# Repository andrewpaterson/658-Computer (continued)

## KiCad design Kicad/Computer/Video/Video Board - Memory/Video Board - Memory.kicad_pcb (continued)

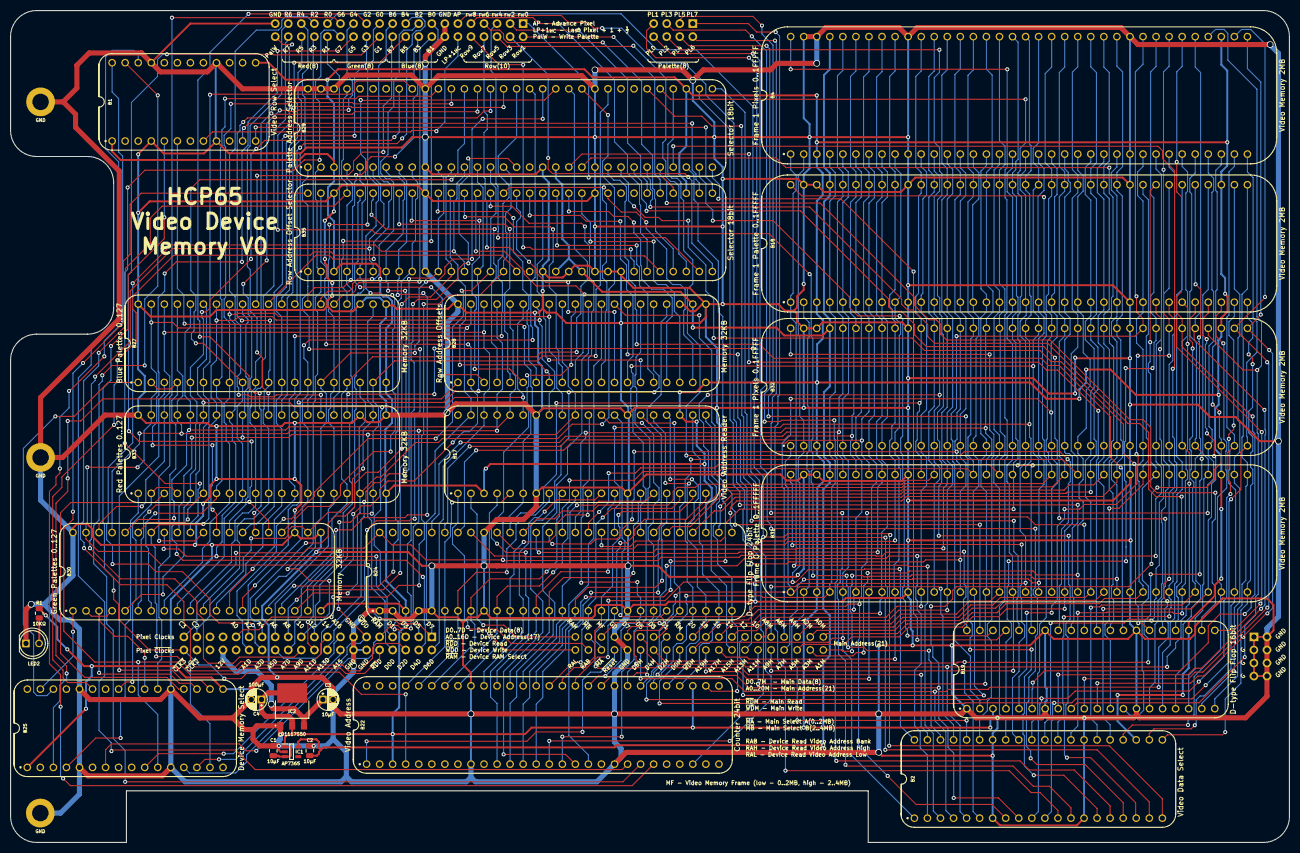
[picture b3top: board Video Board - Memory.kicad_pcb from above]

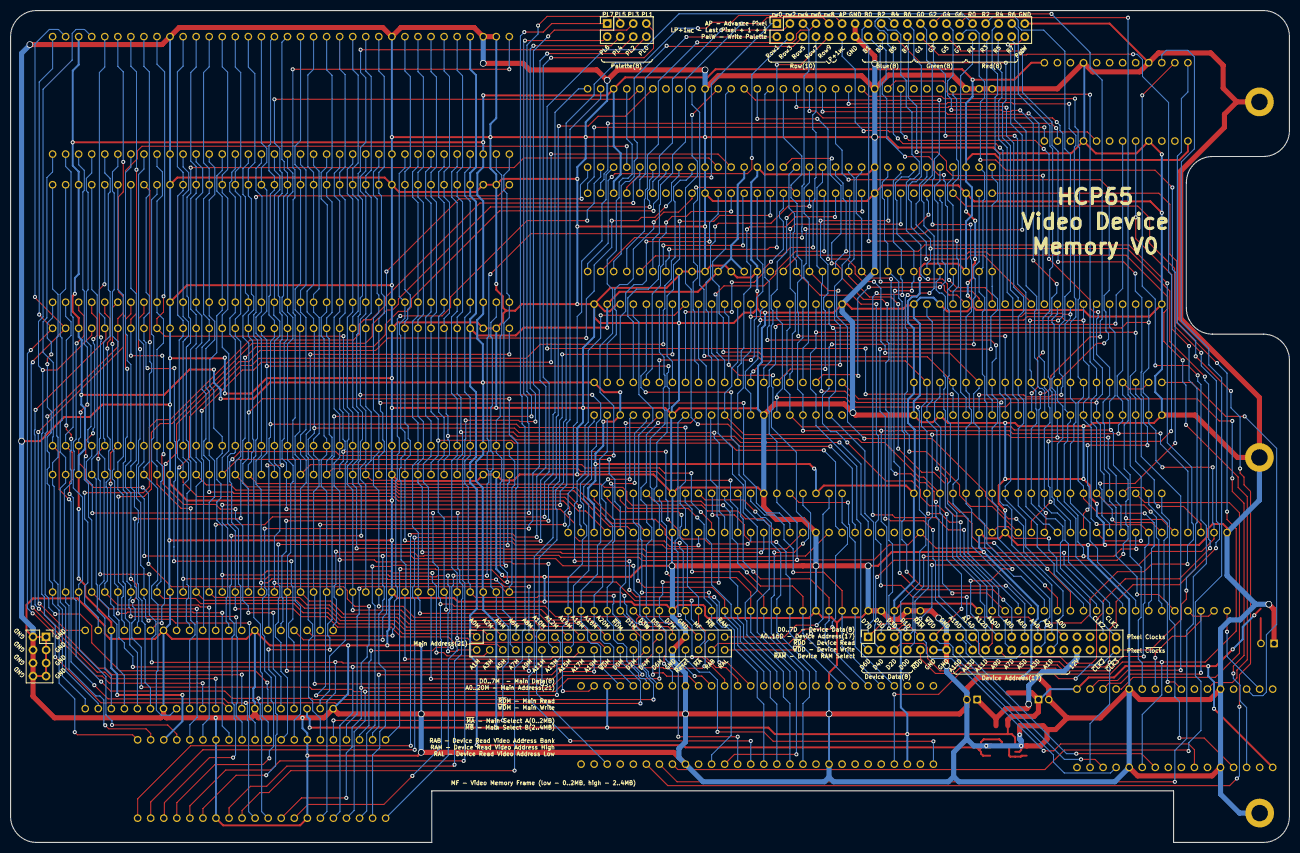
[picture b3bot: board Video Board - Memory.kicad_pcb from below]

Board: 2 copper layers, 248.9 x 161.9 mm, 33 parts (5 on the bottom side), 263 nets.

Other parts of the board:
J5: Conn_01x08_Pin; PinSocket_2x04_P2.54mm_Vertical

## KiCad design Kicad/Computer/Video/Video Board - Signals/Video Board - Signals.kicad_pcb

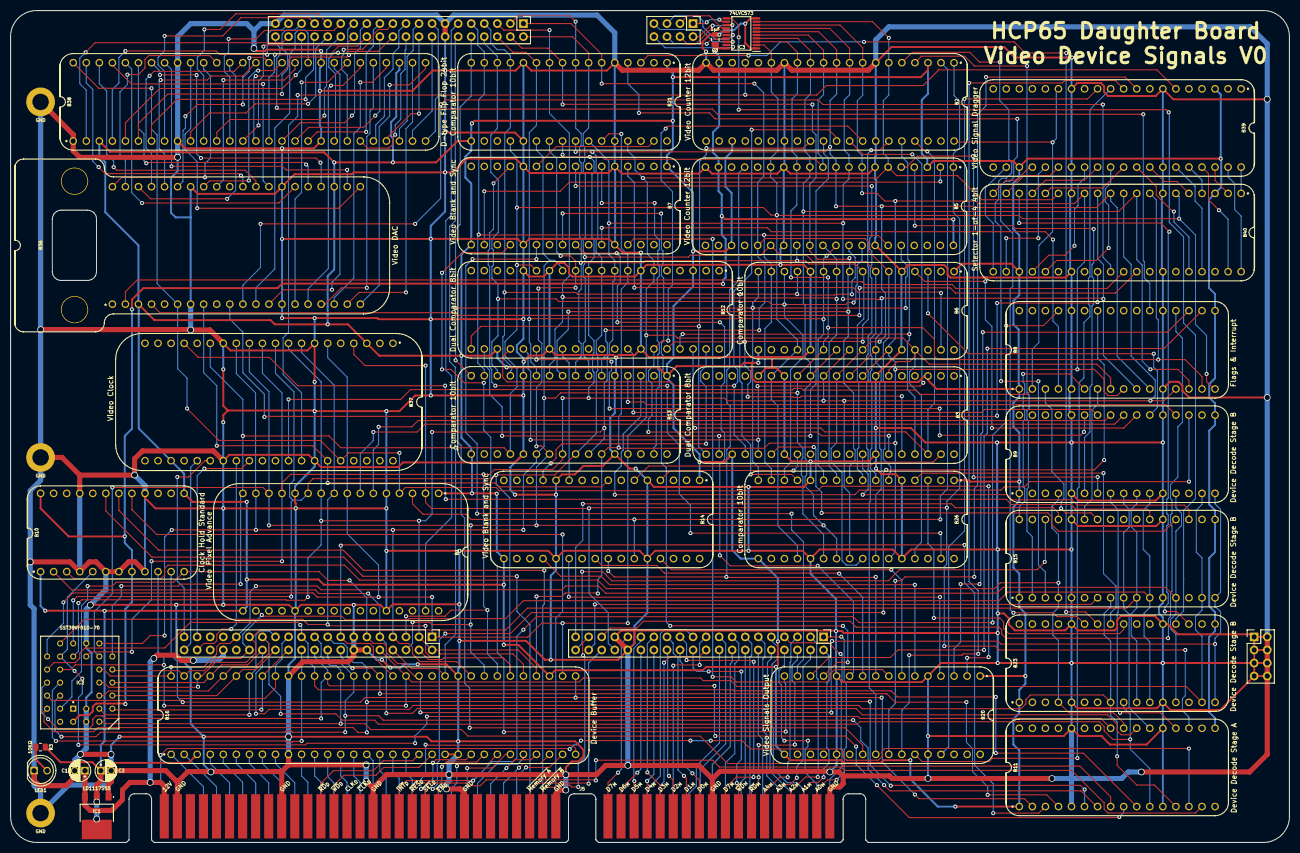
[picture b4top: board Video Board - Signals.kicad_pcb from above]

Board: 2 copper layers, 248.9 x 161.9 mm, 41 parts (0 on the bottom side), 268 nets.

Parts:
B1: Video Pixel Advance; HCP65_Video_Pixel_Advance
B2, B5: Video Counter 12bit; HCP65_Video_Counter_12bit
B3, B12: Dual Comparator 8bit; HCP65_Dual_Comparator_8bit
B6, B13, B21, B26: Comparator 10bit; HCP65_Comparator_10bit
B7, B14: Video Blank and Sync; HCP65_Video_Blank_and_Sync
B8: Flags & Interrupt; HCP65_Flags_Interrupt
B9, B15, B23: Device Decode Stage B; HCP65_Device_Decode_Stage_B
B10: Clock Hold Standard; HCP65_Clock_Hold_Standard
B11: Device Decode Stage A; HCP65_Device_Decode_Stage_A
B16: Device Buffer; HCP65_Device_Buffer
B20: Video Signals Output; HCP65_Video_Output_Signals
B36: Video DAC; HCP65_Video_DAC
B37: Video Clock; HCP65_Video_Clock
B38: D-type Flip Flop 24bit; HCP65_D_Flip_Flop_24bit
B39: Video Signal Dragger; HCP65_Video_Signal_Dragger
B40: Selector 1-of-4 4bit with Input; HCP65_Selector_1_of_4_4bit_with_Input
C1: 10μF; CP_Radial_D4.0mm_P2.00mm
C2: 100μF; CP_Radial_D4.0mm_P2.00mm
C3: 1μF; C_0805
H1, H9, H19: MountingHole_Pad; HCP65_MountingHole_M3_
IC1: LD1117S50C; LD1117S33C
IC2: SST39VF010-70-4I-NHE; 5408803224008
IC3: 74LVC573APW,118; SOP65P640X110-20N
J1, J6: Conn_01x08_Pin; PinHeader_2x04_P2.54mm_Vertical
J2, J3, J4: Conn_01x40_Pin; PinHeader_2x20_P2.54mm_Vertical
J5: 395-098-520-350; 98pin Edge Connector
LED1: LED; LED_D5.0mm
R3: 10KΩ; R_0805

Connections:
12V: C1.1, IC1.3 (15VIn), J4.34, J5.B1
/3.3V: B2.19 (IR0), B5.19 (IR0), B5.40 (~CLK), B10.8 (H0_{REG}), B10.24 (3.3V), C3.2, IC2.32 (3V), IC3.20 (3V)
/5V: B1.1 (5V), B1.17 (5V), B2.3 (5V), B2.23 (5V), B3.3 (5V), B3.23 (5V), B5.3 (5V), B5.23 (5V), B6.1 (5V), B6.17 (5V), B7.1 (5V), B7.17 (5V), B8.1 (5V), B8.17 (5V), B9.1 (5V), B9.17 (5V), B10.1 (5V), B10.13 (5V), B11.1 (5V), B11.17 (5V), B12.3 (5V), B12.23 (5V), B13.1 (5V), B13.17 (5V), B14.1 (5V), B14.17 (5V), B15.1 (5V), B15.17 (5V), B16.3 (5V), B16.35 (5V), B20.1 (5V), B20.17 (5V), B21.1 (5V), B21.17 (5V), B23.1 (5V), B23.17 (5V), B26.1 (5V), B26.17 (5V), B36.3 (5V), B36.23 (5V), B37.3 (5V), B37.23 (5V), B38.3 (5V), B38.31 (5V), B39.3 (5V), B39.23 (5V), B40.3 (5V), B40.23 (5V), C2.1, IC1.2 (5.0VOut), IC1.4 (5.0VOut), R3.2
/A0: B9.13 (A0), B15.13 (A0), B16.64 (A0), B23.13 (A0), IC2.12 (A0), J4.31
/A1: B9.11 (A1), B15.11 (A1), B16.63 (A1), B23.11 (A1), IC2.11 (A1), J4.30
/A2: B9.10 (A2), B15.10 (A2), B16.62 (A2), B23.10 (A2), IC2.10 (A2), J4.29
/A3: B11.13 (A3), B15.8 (~E2), B16.61 (A3), B23.8 (~E2), IC2.9 (A3), J4.28
/A4: B11.11 (A4), B16.60 (A4), B23.9 (E3), IC2.8 (A4), J4.27
/A5: B16.59 (A5), IC2.7 (A5), J4.26
/A6: B16.58 (A6), IC2.6 (A6), J4.25
/A7: B16.57 (A7), IC2.5 (A7), J4.24
/A8: B16.56 (A8), IC2.27 (A8), J4.23
/A9: B16.54 (A9), IC2.26 (A9), J4.22
/A10: B11.10 (A10), B16.53 (A10), IC2.23 (A10), J4.21
/A11: B11.9 (A11), B16.52 (A11), IC2.25 (A11), J4.20
/A12: B11.8 (A12), B16.51 (A12), IC2.4 (A12), J4.19
/A13: B11.7 (A13), B16.50 (A13), IC2.28 (A13), J4.18
/A14: B11.6 (A14), B16.49 (A14), IC2.29 (A14), J4.17
/A15: B11.4 (A15), B16.48 (A15), J4.16
/A16: B11.3 (A16), B16.47 (A16), J4.15
/Advance Pixel: B1.31 (Selected_Pattern), J3.11
/Blue0: B38.28 (IN0), J3.15
/Blue1: B38.27 (IN1), J3.16
/Blue2: B38.26 (IN2), J3.17
/Blue3: B38.25 (IN3), J3.18
/Blue4: B38.24 (IN4), J3.19
/Blue5: B38.23 (IN5), J3.20
/Blue6: B38.22 (IN6), J3.21
/Blue7: B38.21 (IN7), J3.22
/D0: B1.16 (D0), B2.15 (D0), B3.15 (D0), B5.15 (D0), B6.20 (D0), B8.16 (D0), B12.15 (D0), B13.20 (D0), B16.43 (D7), B21.20 (D0), B26.20 (D0), B37.15 (D0), B40.6 (D0), IC2.13 (DQ0), IC3.2 (D0), J4.8
/D1: B1.15 (D1), B2.13 (D1), B3.13 (D1), B5.13 (D1), B6.22 (D1), B8.15 (D1), B12.13 (D1), B13.22 (D1), B16.41 (D6), B21.22 (D1), B26.22 (D1), B37.13 (D1), B40.8 (D1), IC2.14 (DQ1), IC3.3 (D1), J4.7
/D2: B1.14 (D2), B2.12 (D2), B3.12 (D2), B5.12 (D2), B6.23 (D2), B8.14 (D2), B12.12 (D2), B13.23 (D2), B16.40 (D5), B21.23 (D2), B26.23 (D2), B37.12 (D2), B40.9 (D2), IC2.15 (DQ2), IC3.4 (D2), J4.6
/D3: B1.13 (D3), B2.11 (D3), B3.11 (D3), B5.11 (D3), B6.24 (D3), B8.13 (D3), B12.11 (D3), B13.24 (D3), B16.39 (D4), B21.24 (D3), B26.24 (D3), B37.11 (D3), B40.10 (D3), IC2.17 (DQ3), IC3.5 (D3), J4.5
/D4: B1.11 (D4), B2.10 (D4), B3.10 (D4), B5.10 (D4), B6.25 (D4), B8.11 (D4), B12.10 (D4), B13.25 (D4), B16.38 (D3), B21.25 (D4), B26.25 (D4), B37.10 (D4), B40.11 (D4), IC2.18 (DQ4), IC3.6 (D4), J4.4
/D5: B1.10 (D5), B2.9 (D5), B3.9 (D5), B5.9 (D5), B6.26 (D5), B8.10 (D5), B12.9 (D5), B13.26 (D5), B16.37 (D2), B21.26 (D5), B26.26 (D5), B37.9 (D5), B40.12 (D5), IC2.19 (DQ5), IC3.7 (D5), J4.3
/D6: B1.9 (D6), B2.8 (D6), B3.8 (D6), B5.8 (D6), B6.27 (D6), B8.9 (D6), B12.8 (D6), B13.27 (D6), B16.36 (D1), B21.27 (D6), B26.27 (D6), B37.8 (D6), B40.13 (D6), IC2.20 (DQ6), IC3.8 (D6), J4.2
/D7: B1.8 (D7), B2.6 (D7), B3.6 (D7), B5.6 (D7), B6.29 (D7), B8.8 (D7), B12.6 (D7), B13.29 (D7), B16.34 (D0), B21.29 (D7), B26.29 (D7), B37.6 (D7), B40.15 (D7), IC2.21 (DQ7), IC3.9 (D7), J4.1
/First Pixel: B5.17 (CLK), B14.25 (First), B20.9 (First_Pixel)
/First Pixel HC: B7.8 (~CLK), B20.24 (First_Pixel_{OUT})
/First Row: B7.25 (First), B20.11 (First_Row)
/Green0: B38.19 (IN8), J3.23
/Green1: B38.18 (IN9), J3.24
/Green2: B38.17 (IN10), J3.25
/Green3: B38.16 (IN11), J3.26
/Green4: B38.15 (IN12), J3.27
/Green5: B38.14 (IN13), J3.28
/Green6: B38.13 (IN14), J3.29
/Green7: B38.12 (IN15), J3.30
/H3: B2.29 (R3), B3.21 (C0), B12.21 (C0)
/H4: B2.30 (R4), B3.22 (C1), B12.22 (C1)
/H5: B2.31 (R5), B3.24 (C2), B12.24 (C2)
/H6: B2.32 (R6), B3.25 (C3), B12.25 (C3)
/H7: B2.33 (R7), B3.35 (C4), B12.35 (C4)
/H8: B2.35 (R8), B3.36 (C5), B12.36 (C5)
/H9: B2.36 (R9), B3.37 (C6), B12.37 (C6)
/H10: B2.37 (R10), B3.38 (C7), B12.38 (C7)
/HCBlue0: B36.20 (Blue0), B38.29 (OUT0)
/HCBlue1: B36.19 (Blue1), B38.30 (OUT1)
/HCBlue2: B36.18 (Blue2), B38.32 (OUT2)
/HCBlue3: B36.17 (Blue3), B38.33 (OUT3)
/HCBlue4: B36.16 (Blue4), B38.34 (OUT4)
/HCBlue5: B36.15 (Blue5), B38.35 (OUT5)
/HCBlue6: B36.13 (Blue6), B38.36 (OUT6)
/HCBlue7: B36.12 (Blue7), B38.38 (OUT7)
/HCGreen0: B36.32 (Green0), B38.39 (OUT8)
/HCGreen1: B36.33 (Green1), B38.40 (OUT9)
/HCGreen2: B36.35 (Green2), B38.41 (OUT10)
/HCGreen3: B36.36 (Green3), B38.42 (OUT11)
/HCGreen4: B36.37 (Green4), B38.43 (OUT12)
/HCGreen5: B36.38 (Green5), B38.44 (OUT13)
/HCGreen6: B36.39 (Green6), B38.45 (OUT14)
/HCGreen7: B36.40 (Green7), B38.46 (OUT15)
/HCRed0: B36.21 (Red0), B38.47 (OUT16)
/HCRed1: B36.22 (Red1), B38.49 (OUT17)
/HCRed2: B36.24 (Red2), B38.50 (OUT18)
/HCRed3: B36.25 (Red3), B38.51 (OUT19)
/HCRed4: B36.26 (Red4), B38.52 (OUT20)
/HCRed5: B36.28 (Red5), B38.53 (OUT21)
/HCRed6: B36.29 (Red6), B38.54 (OUT22)
/HCRed7: B36.30 (Red7), B38.55 (OUT23)
/Horizontal Blank: B14.29 (Blank), B20.7 (Horizontal_Blank)
/Horizontal Blank C3: B39.33 (Horizontal_Blank__{CYCLE_3}), B40.5 (B2)
/Horizontal Blank C4: B39.24 (Horizontal_Blank__{CYCLE_4}), B40.20 (E2)
/Horizontal Blank HC: B20.27 (Horizontal_Blank_{OUT}), B39.11 (Horizontal_Blank__{HALF_CYCLE})
/Horizontal Blank HC3: B39.38 (Horizontal_Blank__{CYCLE_3H}), B40.2 (A2)
/Horizontal Blank HC4: B39.29 (Horizontal_Blank__{CYCLE_4H}), B40.17 (C2)
/Horizontal Blank _{FINAL}: B36.2 (Horizontal_Blank), B40.31 (Y1)
/Horizontal Sync: B14.22 (Sync), B20.4 (Horizontal_Sync)
/Horizontal Sync C3: B39.32 (Horizontal_Sync__{CYCLE_3}), B40.36 (B3)
/Horizontal Sync C4: B39.22 (Horizontal_Sync__{CYCLE_4}), B40.21 (E3)
/Horizontal Sync HC: B20.29 (Horizontal_Sync_{OUT}), B39.12 (Horizontal_Sync__{HALF_CYCLE})
/Horizontal Sync HC3: B39.37 (Horizontal_Sync__{CYCLE_3H}), B40.39 (A3)
/Horizontal Sync HC4: B39.28 (Horizontal_Sync__{CYCLE_4H}), B40.24 (C3)
/Horizontal Sync Polarity: B8.19 (F1), B20.3 (Horizontal_Sync_Polarity)
/Horizontal Sync _{FINAL}: B36.4 (Horizontal_Sync), B40.32 (Y0)
/Last Pixel+1: B14.24 (Last+1), B20.10 (Last_Pixel+1)
/Last Pixel+1 HC: B20.23 (Last_Pixel+1_{OUT}), J3.12
/Last Row+1: B7.24 (Last+1), B20.13 (Last_Row+1)
/Memory Frame: B8.20 (F2), J2.35
/PL0: IC3.19 (Q0), J1.8
/PL1: IC3.18 (Q1), J1.7
/PL2: IC3.17 (Q2), J1.6
/PL3: IC3.16 (Q3), J1.5
/PL4: IC3.15 (Q4), J1.4
/PL5: IC3.14 (Q5), J1.3
/PL6: IC3.13 (Q6), J1.2
/PL7: IC3.12 (Q7), J1.1
/Palette Write: B8.22 (F3), J3.40
/Pixel CLK_{0}: B1.4 (CLK), B20.2 (~Pixel_CLK), B36.6 (~CLK), B37.36 (Pixel_CLK_{0}), B38.56 (CLK)
/Pixel CLK_{1}: B2.17 (CLK), B37.33 (Pixel_CLK_{1}), B39.6 (Pixel_CLK)
/Pixel CLK_{2}: B37.29 (Pixel_CLK_{2}), J4.37
/Pixel CLK_{3}: B37.26 (Pixel_CLK_{3}), J4.39
/Read Address Bank: B15.7 (Y4_{R}), J2.38
/Read Address High: B15.29 (Y3_{R}), J2.39
/Read Address Low: B15.30 (Y2_{R}), J2.40
/Read Flags: B8.6 (Read_Flags), B15.32 (Y0_{R})
/Read Horizontal High: B2.4 (Read_Count_High), B15.2 (Y7_{R})
/Read Horizontal Low: B2.5 (Read_Count_Low), B15.3 (Y6_{R})
/Read Vertical High: B5.4 (Read_Count_High), B9.6 (Y5_{R})
/Read Vertical Low: B5.5 (Read_Count_Low), B9.7 (Y4_{R})
/Red0: B38.11 (IN16), J3.31
/Red1: B38.10 (IN17), J3.32
/Red2: B38.8 (IN18), J3.33
/Red3: B38.7 (IN19), J3.34
/Red4: B38.6 (IN20), J3.35
/Red5: B38.5 (IN21), J3.36
/Red6: B38.4 (IN22), J3.37
/Red7: B38.2 (IN23), J3.38
/Row0: B5.25 (R0), B6.6 (C0), B13.6 (C0), B21.6 (C0), B26.6 (C0), J3.1
/Row1: B5.26 (R1), B6.7 (C1), B13.7 (C1), B21.7 (C1), B26.7 (C1), J3.2
/Row2: B5.28 (R2), B6.8 (C2), B13.8 (C2), B21.8 (C2), B26.8 (C2), J3.3
/Row3: B5.29 (R3), B6.9 (C3), B13.9 (C3), B21.9 (C3), B26.9 (C3), J3.4
/Row4: B5.30 (R4), B6.10 (C4), B13.10 (C4), B21.10 (C4), B26.10 (C4), J3.5
/Row5: B5.31 (R5), B6.11 (C5), B13.11 (C5), B21.11 (C5), B26.11 (C5), J3.6
/Row6: B5.32 (R6), B6.13 (C6), B13.13 (C6), B21.13 (C6), B26.13 (C6), J3.7
/Row7: B5.33 (R7), B6.14 (C7), B13.14 (C7), B21.14 (C7), B26.14 (C7), J3.8
/Row8: B5.35 (R8), B6.15 (C8), B13.15 (C8), B21.15 (C8), B26.15 (C8), J3.9
/Row9: B5.36 (R9), B6.16 (C9), B13.16 (C9), B21.16 (C9), B26.16 (C9), J3.10
/Vertical Blank: B7.29 (Blank), B20.8 (Vertical_Blank)
/Vertical Blank C3: B39.36 (Vertical_Blank__{CYCLE_3}), B40.4 (B0)
/Vertical Blank C4: B39.26 (Vertical_Blank__{CYCLE_4}), B40.19 (E0)
/Vertical Blank HC: B20.25 (Vertical_Blank_{OUT}), B39.9 (Vertical_Blank__{HALF_CYCLE})
/Vertical Blank HC3: B39.40 (Vertical_Blank__{CYCLE_3H}), B40.1 (A0)
/Vertical Blank HC4: B39.31 (Vertical_Blank__{CYCLE_4H}), B40.16 (C0)
/Vertical Blank _{FINAL}: B36.10 (Vertical_Blank), B40.29 (Y3)
/Vertical Sync: B7.22 (Sync), B20.15 (Vertical_Sync)
/Vertical Sync C3: B39.35 (Vertical_Sync__{CYCLE_3}), B40.37 (B1)
/Vertical Sync C4: B39.25 (Vertical_Sync__{CYCLE_4}), B40.22 (E1)
/Vertical Sync HC: B20.26 (Vertical_Sync_{OUT}), B39.10 (Vertical_Sync__{HALF_CYCLE})
/Vertical Sync HC3: B39.39 (Vertical_Sync__{CYCLE_3H}), B40.40 (A1)
/Vertical Sync HC4: B39.30 (Vertical_Sync__{CYCLE_4H}), B40.25 (C1)
/Vertical Sync Polarity: B8.18 (F0), B20.14 (Vertical_Sync_Polarity)
/Vertical Sync _{FINAL}: B36.11 (Vertical_Sync), B40.30 (Y2)
/Write Clear Interrupt: B8.3 (Write_Clear_Interrupt), B15.26 (Y1_{W})
/Write Clock Select: B15.22 (Y5_{W}), B37.17 (Write_Clock_Select)
/Write Flags: B8.7 (Write_Flags), B15.27 (Y0_{W})
/Write Horizontal Back Porch End: B9.26 (Y1_{W}), B12.33 (Write_B)
/Write Horizontal Back Porch Start: B9.27 (Y0_{W}), B12.26 (Write_A)
/Write Horizontal Front Porch Start: B3.26 (Write_A), B15.20 (Y6_{W})
/Write Horizontal Shift Pattern High: B1.7 (Write_Pattern_High), B9.24 (Y3_{W})
/Write Horizontal Shift Pattern Low: B1.6 (Write_Pattern_Low), B9.25 (Y2_{W})
/Write Horiztonal Sync Start: B3.33 (Write_B), B15.19 (Y7_{W})
/Write Palette Byte: B23.20 (Y6_{W}), IC3.11 (LE)
/Write Vertical Back Porch End High: B23.24 (Y3_{W}), B26.3 (Write_A_High)
/Write Vertical Back Porch End Low: B23.25 (Y2_{W}), B26.4 (Write_A_Low)
/Write Vertical Back Porch Start High: B21.3 (Write_A_High), B23.26 (Y1_{W})
/Write Vertical Back Porch Start Low: B21.4 (Write_A_Low), B23.27 (Y0_{W})
/Write Vertical Front Porch Start High: B6.3 (Write_A_High), B9.22 (Y5_{W})
/Write Vertical Front Porch Start Low: B6.4 (Write_A_Low), B9.23 (Y4_{W})
/Write Vertical Sync Start High: B9.19 (Y7_{W}), B13.3 (Write_A_High)
/Write Vertical Sync Start Low: B9.20 (Y6_{W}), B13.4 (Write_A_Low)
/Write Video Signal Delay: B23.19 (Y7_{W}), B40.18 (Write_Select)
/~A3: B9.8 (~E2), B11.20 (~A3)
/~A4: B9.9 (E3), B11.22 (~A4), B15.9 (E3)
/~Device RAM: B10.2 (~Device_RAM), B11.23 (~Device_RAM), J4.9
/~Device ROM: B10.5 (~Device_ROM), B11.25 (~Device_ROM), IC2.22 (~CE)
/~Device Registers: B9.4 (~Device_Registers), B10.3 (~Device_Registers), B11.24 (~Device_Registers), B15.4 (~Device_Registers), B23.4 (~Device_Registers)
/~Device Select: B10.11 (~Device_Select), B11.2 (~Device_Select), B16.33 (Deivce_~CS)
/~Horizontal Back Porch End _{CMP}: B12.39 (~B=C), B14.13 (~Back_Porch_End)
/~Horizontal Back Porch Start _{CMP}: B12.28 (~A=C), B14.11 (~Back_Porch_Start)
/~Horizontal Blank: B1.3 (Enable_Pattern), B2.2 (~Load), B14.27 (~Blank)
/~Horizontal Front Porch Start _{CMP}: B3.28 (~A=C), B14.4 (~Front_Porch_Start)
/~Horizontal Sync Start _{CMP}: B3.39 (~B=C), B14.6 (~Sync_Start)
/~Horizontal Sync: B14.20 (~Sync), B20.6 (~Horizontal_Sync)
/~Pixel CLK_{0}: B14.8 (~CLK), B36.8 (CLK), B37.35 (~Pixel_CLK_{0})
/~Pixel CLK_{1}: B2.40 (~CLK), B8.2 (Interrupt_CLK), B37.32 (~Pixel_CLK_{1}), B39.15 (~Pixel_CLK)
/~Pixel CLK_{2}: B37.28 (~Pixel_CLK_{2}), J4.38
/~Pixel CLK_{3}: B37.25 (~Pixel_CLK_{3}), J4.40
/~RD: B9.15 (~RD), B10.10 (~RD), B15.15 (~RD), B16.46 (~RD), B23.15 (~RD), IC2.24 (~OE), J4.10
/~Reset: B1.2 (~Reset), B2.1 (~Reset), B5.1 (~Reset), B11.19 (~Reset_{OUT}), B37.4 (~Reset), J2.34
/~Vertical Back Porch End: B5.2 (~Load), B7.18 (~Back_Porch_End)
/~Vertical Back Porch End _{CMP}: B7.13 (~Back_Porch_End), B26.31 (~C=A)
/~Vertical Back Porch Start _{CMP}: B7.11 (~Back_Porch_Start), B21.31 (~C=A)
/~Vertical Blank: B7.27 (~Blank), B8.4 (~Set_Interrupt_on_CLK)
/~Vertical Front Porch Start _{CMP}: B6.31 (~C=A), B7.4 (~Front_Porch_Start)
/~Vertical Sync Start _{CMP}: B7.6 (~Sync_Start), B13.31 (~C=A)
/~Vertical Sync: B7.20 (~Sync), B20.16 (~Vertical_Sync)
/~WD: B9.16 (~WD), B10.12 (~WD), B15.16 (~WD), B16.45 (~WD), B23.16 (~WD), IC2.31 (~WE), J4.11
AD0: B16.1 (A0_{IN}), J5.A4
AD1: B16.2 (A1_{IN}), J5.A5
AD2: B16.4 (A2_{IN}), J5.A6
AD3: B16.5 (A3_{IN}), J5.A7
AD4: B16.6 (A4_{IN}), J5.A8
AD5: B16.7 (A5_{IN}), J5.A9
AD6: B16.8 (A6_{IN}), J5.A10
AD7: B16.9 (A7_{IN}), J5.A11
AD8: B16.11 (A8_{IN}), J5.A12
AD9: B16.12 (A9_{IN}), J5.A13
AD10: B16.13 (A10_{IN}), J5.A14
AD11: B16.14 (A11_{IN}), J5.A15
AD12: B16.15 (A12_{IN}), J5.A16
AD13: B16.16 (A13_{IN}), J5.A17
AD14: B16.17 (A14_{IN}), J5.A18
AD15: B16.18 (A15_{IN}), J5.A19
AD16: B16.19 (A16_{IN}), J5.A20
AM0: J2.1, J5.D17
AM1: J2.2, J5.D16
AM2: J2.3, J5.D15
AM3: J2.4, J5.D14
AM4: J2.5, J5.D13
AM5: J2.6, J5.D12
AM6: J2.7, J5.C18
AM7: J2.8, J5.C17
AM8: J2.9, J5.C16
AM9: J2.10, J5.C15
AM10: J2.11, J5.C14
AM11: J2.12, J5.C13
AM12: J2.13, J5.C12
AM13: J2.14, J5.C11
AM14: J2.15, J5.C10
AM15: J2.16, J5.C9
AM16: J2.17, J5.C8
AM17: J2.18, J5.C7
AM18: J2.19, J5.C6
AM19: J2.20, J5.C5
AM20: J2.21, J5.C4
DD0: B16.31 (D0_{IN/OUT}), J5.A28
DD1: B16.30 (D1_{IN/OUT}), J5.A27
DD2: B16.29 (D2_{IN/OUT}), J5.A26
DD3: B16.28 (D3_{IN/OUT}), J5.A25
DD4: B16.27 (D4_{IN/OUT}), J5.A24
DD5: B16.26 (D5_{IN/OUT}), J5.A23
DD6: B16.25 (D6_{IN/OUT}), J5.A22
DD7: B16.24 (D7_{IN/OUT}), J5.A21
DM0: J2.24, J5.D8
DM1: J2.25, J5.D7
DM2: J2.26, J5.D6
DM3: J2.27, J5.D5
DM4: J2.28, J5.D4
DM5: J2.29, J5.D3
DM6: J2.30, J5.D2
DM7: J2.31, J5.D1
D~RD: B16.20 (~RD_{IN}), J5.B13
D~WD: B16.21 (~WD_{IN}), J5.B14
GND: B1.5 (GND), B1.12 (GND), B1.21 (GND), B1.28 (GND), B2.7 (GND), B2.14 (GND), B2.20 (IR1), B2.27 (GND), B2.34 (GND), B3.7 (GND), B3.14 (GND), B3.16 (~OE), B3.27 (GND), B3.34 (GND), B5.7 (GND), B5.14 (GND), B5.20 (IR1), B5.27 (GND), B5.34 (GND), B6.5 (GND), B6.12 (GND), B6.21 (GND), B6.28 (GND), B7.5 (GND), B7.12 (GND), B7.21 (GND), B7.28 (GND), B8.5 (GND), B8.12 (GND), B8.21 (GND), B8.28 (GND), B9.5 (GND), B9.12 (GND), B9.21 (GND), B9.28 (GND), B10.4 (GND), B10.6 (H2_{REG}), B10.7 (H1_{REG}), B10.9 (GND), B10.16 (GND), B10.21 (GND), B11.5 (GND), B11.12 (GND), B11.21 (GND), B11.28 (GND), B12.7 (GND), B12.14 (GND), B12.16 (~OE), B12.27 (GND), B12.34 (GND), B13.5 (GND), B13.12 (GND), B13.21 (GND), B13.28 (GND), B14.5 (GND), B14.12 (GND), B14.21 (GND), B14.28 (GND), B15.5 (GND), B15.12 (GND), B15.21 (GND), B15.28 (GND), B16.10 (GND), B16.22 (S_{IN}), B16.23 (GND), B16.42 (GND), B16.55 (GND), B20.5 (GND), B20.12 (GND), B20.21 (GND), B20.28 (GND), B21.5 (GND), B21.12 (GND), B21.21 (GND), B21.28 (GND), B23.5 (GND), B23.12 (GND), B23.21 (GND), B23.28 (GND), B26.5 (GND), B26.12 (GND), B26.21 (GND), B26.28 (GND), B36.7 (GND), B36.14 (GND), B36.27 (GND), B36.34 (GND), B37.7 (GND), B37.14 (GND), B37.27 (GND), B37.34 (GND), B38.1 (~OE), B38.9 (GND), B38.20 (GND), B38.37 (GND), B38.48 (GND), B39.7 (GND), B39.14 (GND), B39.27 (GND), B39.34 (GND), B40.7 (GND), B40.14 (GND), B40.27 (GND), B40.34 (GND), C1.2, C2.2, C3.1, H1.1 (GND), H9.1 (GND), H19.1 (GND), IC1.1 (GND), IC2.2 (A16), IC2.3 (A15), IC2.16 (GND), IC3.1 (~OE), IC3.10 (GND), J2.32, J2.33, J3.13, J3.14, J3.39, J4.12, J4.13, J4.14, J5.B2, J5.B10, J5.B17, J5.B24, J5.B31, J5.D9, J5.D18, J6.1, J6.2, J6.3, J6.4, J6.5, J6.6, J6.7, J6.8, LED1.1 (K)
HD0: B10.17 (H0_{OUT}), J5.A31
HD1: B10.18 (H1_{OUT}), J5.A30
HD2: B10.19 (H2_{OUT}), J5.A29
unnamed: LED1.2 (A), R3.1
~Device Enable: B8.26 (~Enable), J5.B22
~Device Interrupt: B8.29 (~INT), J5.B19
~Main RD: J2.23, J5.D10
~Main WD: J2.22, J5.D11
~Memory A: J2.36, J5.B29
~Memory B: J2.37, J5.B30
~Reset Device: B11.15 (~Reset_{IN1}), J5.B20
~Reset System: B11.14 (~Reset_{IN2}), J5.A1
~Select Device: B16.32 (Deivce_~CS_{IN}), J5.B21

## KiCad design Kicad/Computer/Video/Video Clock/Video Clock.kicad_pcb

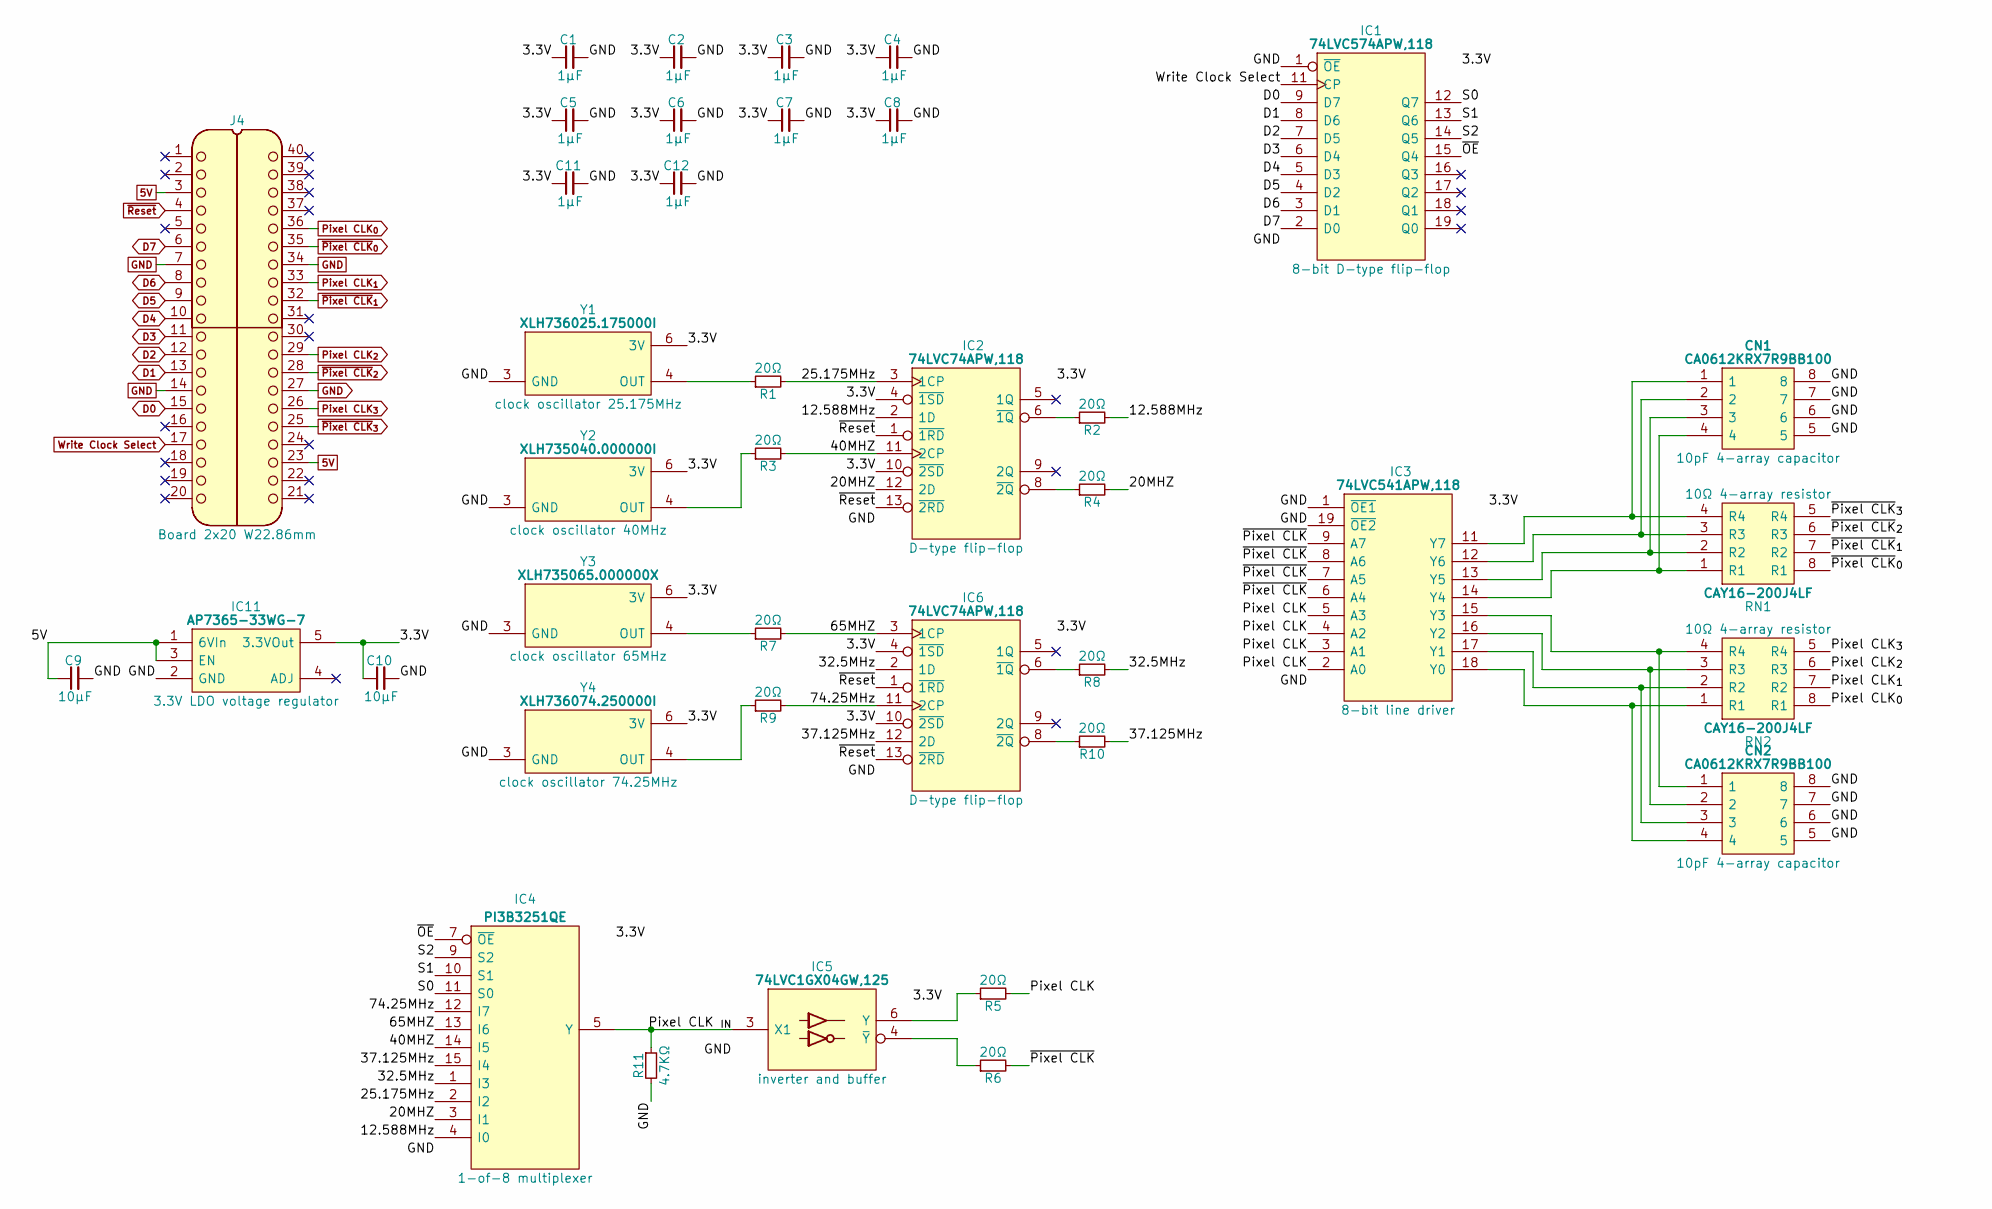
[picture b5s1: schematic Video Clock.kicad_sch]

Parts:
C1, C2, C3, C4, C5, C6, C7, C8, C11, C12: 1μF; C_0805
C9, C10: 10μF; C_0805
CN1, CN2: CA0612KRX7R9BB100; Manufacturer_Part_Number CA0612KRX7R9BB102; Mouser Part Number 603-CA612KRX7R9BB102
IC1: 74LVC574APW,118; SOP65P640X110-20N; Manufacturer_Part_Number 74LVC574APW,118; Mouser Part Number 771-74LVC574APW-T
IC2, IC6: 74LVC74APW,118; SOP65P640X110-14N; Mouser Part Number 771-74LVC74APW-T
IC3: 74LVC541APW,118; SOP65P640X110-20N; Mouser Part Number 771-74LVC541APW-T
IC4: PI3B3251QE; SOP64P599X175-16N; Manufacturer_Part_Number PI3B3251QE; Mouser Part Number 729-PI3B3251QE
IC5: 74LVC1GX04GW,125; SOP65P210X110-6N; Manufacturer_Part_Number 74LVC1GX04GW,125; Mouser Part Number 771-74LVC1GX04GW-G
IC11: AP7365-33WG-7; SOT95P285X130-5N; Manufacturer_Part_Number AP7365-33WG-7; Mouser Part Number 621-AP7365-33WG-7
J4: Board 2x20 W22.86mm; DIP-40_Board_W22.86mm
R1, R2, R3, R4, R5, R6, R7, R8, R9, R10: 20Ω; R_0805
R11: 4.7KΩ; R_0805
RN1, RN2: CAY16-200J4LF; CAY16-F4; Manufacturer_Part_Number CAY16-331J4LF; Mouser Part Number 652-CAY16-331J4LF
Y1: XLH736025.175000I; XLH736074250000I; Manufacturer_Part_Number XLH736025.175000I; Mouser Part Number 972-LH736025.175000I
Y2: XLH735040.000000I; XLH736074250000I; Manufacturer_Part_Number XLH735040.000000I; Mouser Part Number 972-LH735040.000000I
Y3: XLH735065.000000X; XLH735065000000X; Manufacturer_Part_Number XLH735065.000000X; Mouser Part Number 972-XLH735065000000X
Y4: XLH736074.250000I; XLH736074250000I; Manufacturer_Part_Number XLH736074.250000I; Mouser Part Number 972-XLH736074250000I

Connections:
5V: C9.1, IC11.1 (6VIn), IC11.3 (EN), J4.3, J4.23
/3.3V: C1.1, C2.1, C3.1, C4.1, C5.1, C6.1, C7.1, C8.1, C10.1, C11.1, C12.1, IC1.20 (3V), IC2.4 (~1SD), IC2.10 (~2SD), IC2.14 (3V), IC3.20 (3V), IC4.16 (3V), IC5.5 (3V), IC6.4 (~1SD), IC6.10 (~2SD), IC6.14 (3V), IC11.5 (3.3VOut), Y1.6 (3V), Y2.6 (3V), Y3.6 (3V), Y4.6 (3V)
/12.588MHz: IC2.2 (1D), IC4.4 (I0), R2.2
/20MHZ: IC2.12 (2D), IC4.3 (I1), R4.2
/25.175MHz: IC2.3 (1CP), IC4.2 (I2), R1.2
/32.5MHz: IC4.1 (I3), IC6.2 (1D), R8.2
/37.125MHz: IC4.15 (I4), IC6.12 (2D), R10.2
/40MHZ: IC2.11 (2CP), IC4.14 (I5), R3.2
/65MHZ: IC4.13 (I6), IC6.3 (1CP), R7.2
/74.25MHz: IC4.12 (I7), IC6.11 (2CP), R9.2
/Pixel CLK: IC3.2 (A0), IC3.3 (A1), IC3.4 (A2), IC3.5 (A3), R5.2
/Pixel CLK _{IN}: IC4.5 (Y), IC5.3 (X1), R11.1
/S0: IC1.12 (Q7), IC4.11 (S0)
/S1: IC1.13 (Q6), IC4.10 (S1)
/S2: IC1.14 (Q5), IC4.9 (S2)
/~OE: IC1.15 (Q4), IC4.7 (~OE)
/~Pixel CLK: IC3.6 (A4), IC3.7 (A5), IC3.8 (A6), IC3.9 (A7), R6.2
D0: IC1.9 (D7), J4.15
D1: IC1.8 (D6), J4.13
D2: IC1.7 (D5), J4.12
D3: IC1.6 (D4), J4.11
D4: IC1.5 (D3), J4.10
D5: IC1.4 (D2), J4.9
D6: IC1.3 (D1), J4.8
D7: IC1.2 (D0), J4.6
GND: C1.2, C2.2, C3.2, C4.2, C5.2, C6.2, C7.2, C8.2, C9.2, C10.2, C11.2, C12.2, CN1.5, CN1.6, CN1.7, CN1.8, CN2.5, CN2.6, CN2.7, CN2.8, IC1.1 (~OE), IC1.10 (GND), IC2.7 (GND), IC3.1 (~OE1), IC3.10 (GND), IC3.19 (~OE2), IC4.8 (GND), IC5.2 (GND), IC6.7 (GND), IC11.2 (GND), J4.7, J4.14, J4.27, J4.34, R11.2, Y1.3 (GND), Y2.3 (GND), Y3.3 (GND), Y4.3 (GND)
unnamed: IC2.6 (~1Q), R2.1
unnamed: IC2.8 (~2Q), R4.1
unnamed: CN2.4, IC3.18 (Y0), RN2.1 (R1)
unnamed: CN2.3, IC3.17 (Y1), RN2.2 (R2)
unnamed: CN2.2, IC3.16 (Y2), RN2.3 (R3)
unnamed: CN2.1, IC3.15 (Y3), RN2.4 (R4)
unnamed: CN1.4, IC3.14 (Y4), RN1.1 (R1)
unnamed: CN1.3, IC3.13 (Y5), RN1.2 (R2)
unnamed: CN1.2, IC3.12 (Y6), RN1.3 (R3)
unnamed: CN1.1, IC3.11 (Y7), RN1.4 (R4)
unnamed: IC5.6 (Y), R5.1
unnamed: IC5.4 (~Y), R6.1
unnamed: IC6.6 (~1Q), R8.1
unnamed: IC6.8 (~2Q), R10.1
unnamed: R1.1, Y1.4 (OUT)
unnamed: R3.1, Y2.4 (OUT)
unnamed: R7.1, Y3.4 (OUT)
unnamed: R9.1, Y4.4 (OUT)
Pixel CLK_{0}: J4.36, RN2.8 (R1)
Pixel CLK_{1}: J4.33, RN2.7 (R2)
Pixel CLK_{2}: J4.29, RN2.6 (R3)
Pixel CLK_{3}: J4.26, RN2.5 (R4)
Write Clock Select: IC1.11 (CP), J4.17
~Pixel CLK_{0}: J4.35, RN1.8 (R1)
~Pixel CLK_{1}: J4.32, RN1.7 (R2)
~Pixel CLK_{2}: J4.28, RN1.6 (R3)
~Pixel CLK_{3}: J4.25, RN1.5 (R4)
~Reset: IC2.1 (~1RD), IC2.13 (~2RD), IC6.1 (~1RD), IC6.13 (~2RD), J4.4

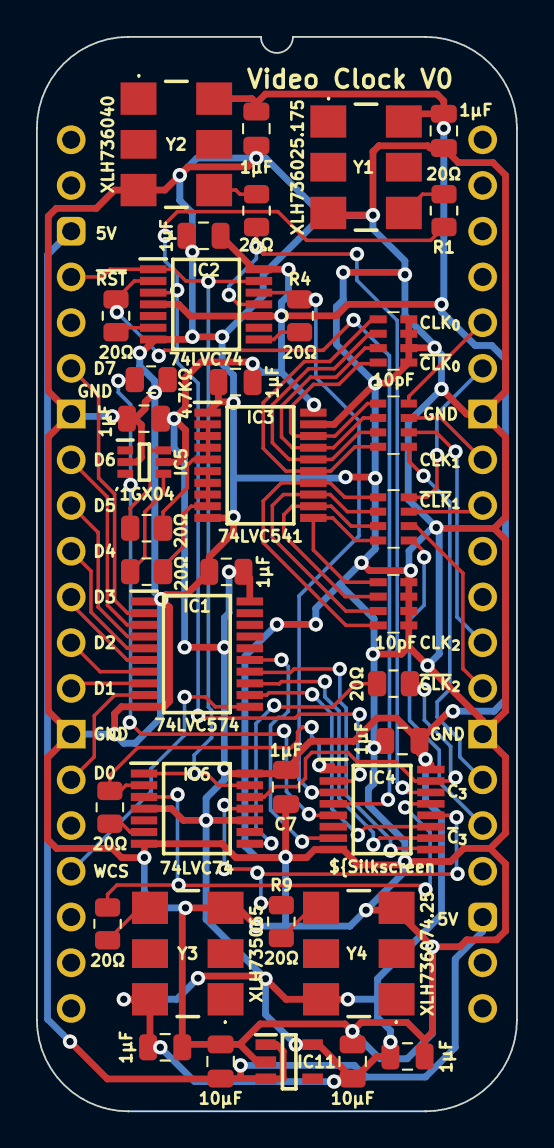
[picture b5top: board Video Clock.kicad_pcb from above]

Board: 2 copper layers, 26.7 x 59.7 mm, 39 parts (0 on the bottom side), 54 nets.
